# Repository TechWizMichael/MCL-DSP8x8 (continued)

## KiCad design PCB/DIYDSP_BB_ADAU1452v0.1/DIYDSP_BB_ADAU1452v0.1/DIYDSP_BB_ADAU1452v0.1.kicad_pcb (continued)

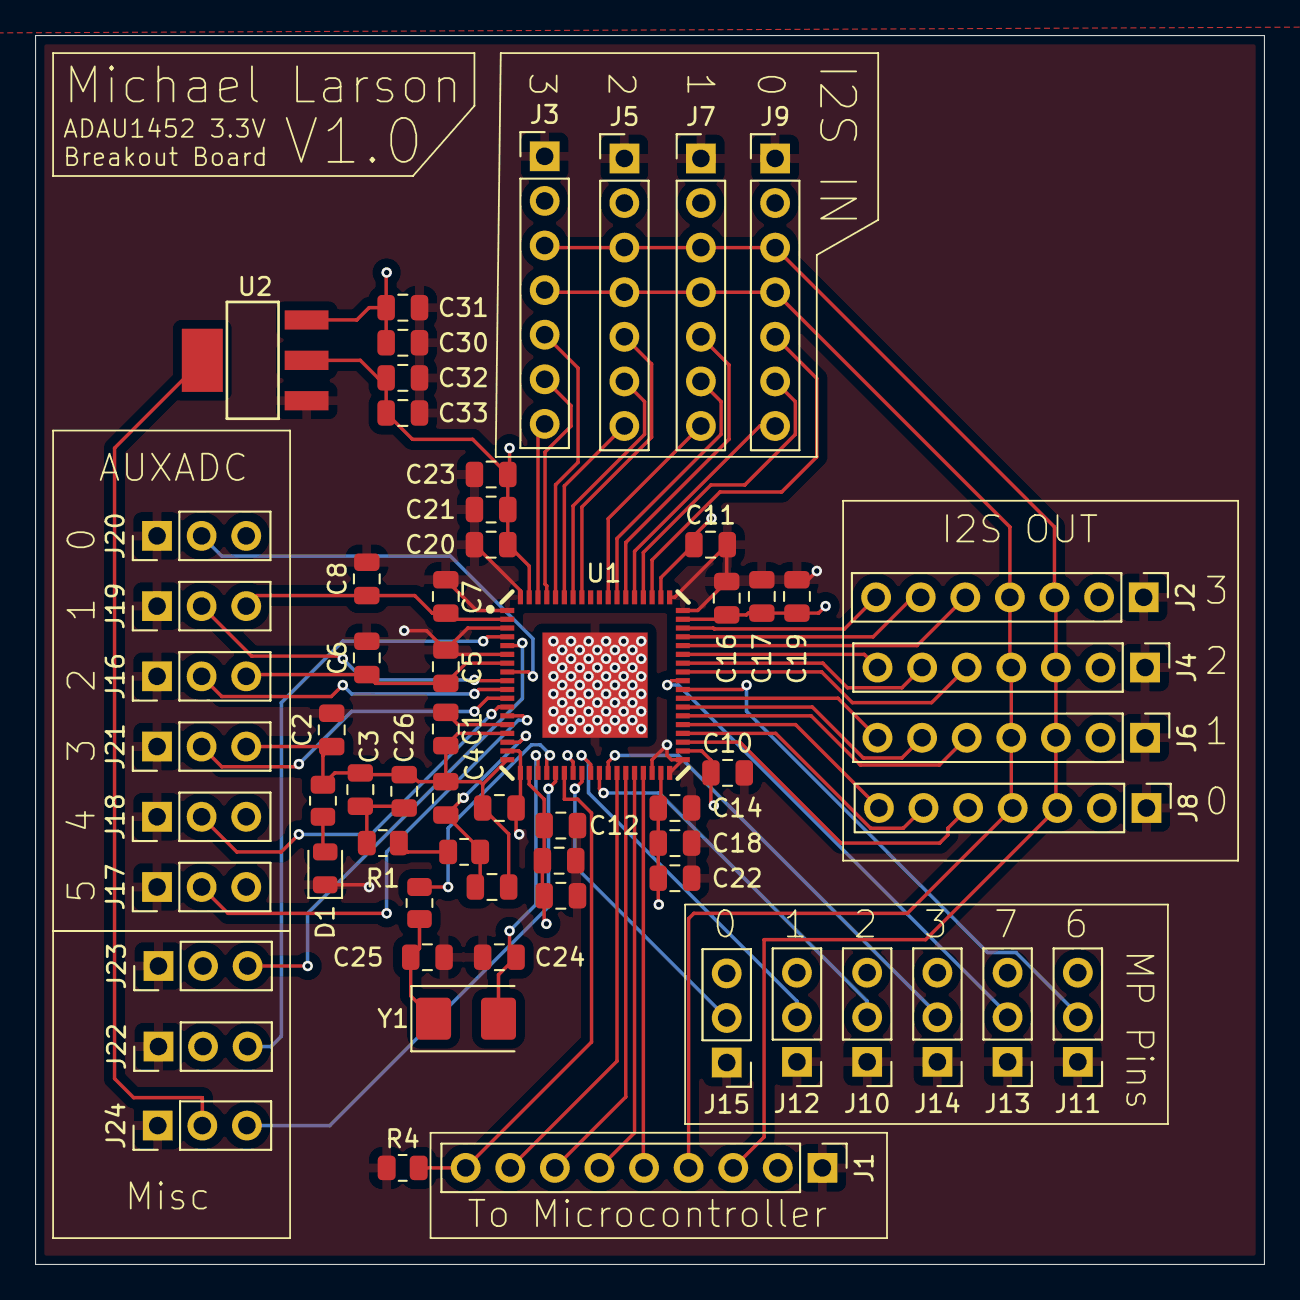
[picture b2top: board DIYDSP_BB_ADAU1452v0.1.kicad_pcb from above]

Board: 4 copper layers, 70.0 x 70.0 mm, 64 parts (0 on the bottom side), 57 nets.

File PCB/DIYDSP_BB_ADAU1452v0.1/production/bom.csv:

Designator,Footprint,Quantity,Value,LCSC Part #
"C1, C10, C11, C13, C17, C18, C21, C30, C32, C5, C7, C9",0805,12,100n,C28233
"C12, C14, C16, C20",0805,4,10n,C1710
"C15, C19, C22, C23",0805,4,1u,C28323
"C2, C31, C33, C6, C8",0805,5,10u,C15850
"C24, C25",0805,2,22p,C1804
C26,0805,1,4.7n,C1744
C27,0805,1,47p,C14857
C3,0805,1,1n,C46653
C4,0805,1,100p,C1790
D1,0805,1,LED,C84256
"R1, R5",0805,2,2.2k,C17520
"R2, R3",0805,2,100,C17408
R4,0805,1,1k,C17513
U1,ADAU1452WBCPZ-RL,1,ADAU1452,C462188
U2,AMS1117-1.2,1,AMS1117-1.2,C2992568
Y1,Crystal_SMD_5032-2Pin_5.0x3.2mm,1,12.288M,C20624119
